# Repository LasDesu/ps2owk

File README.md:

# ps2owk
PS/2 to One-Wire-Keyboard adapter.

Adapter for various retro computer keyboards using only one wire for data transfer. One hardware - multiple firmware.
Currently supported:
- PC-8801MA (type C keyboard, I guess)
- FM-77AV

Original project page: http://zxdesu.byethost32.com/2018/02/13/pc-8801-keyboard-adapter/

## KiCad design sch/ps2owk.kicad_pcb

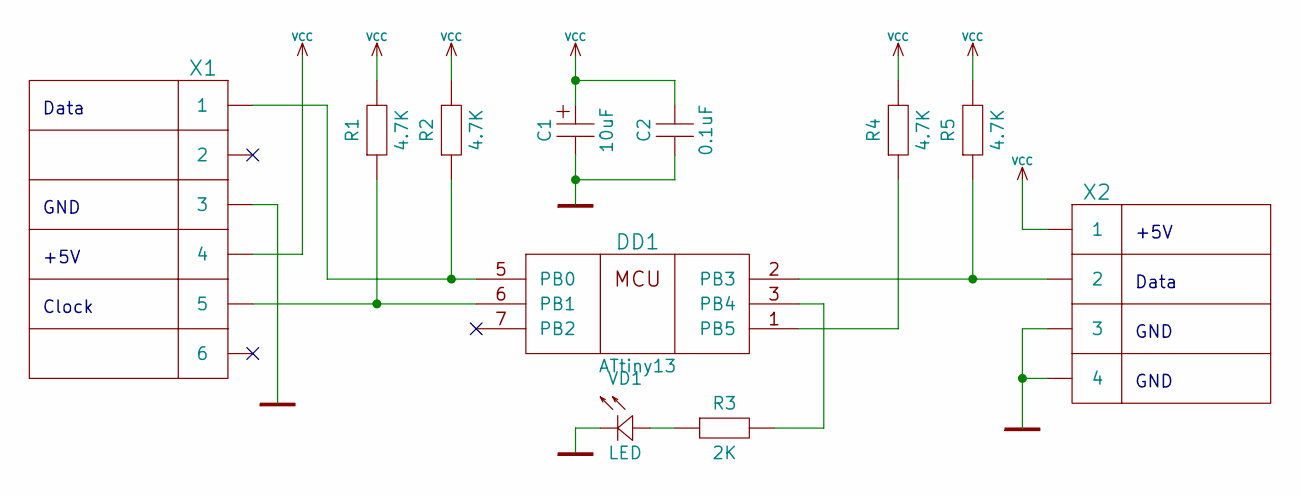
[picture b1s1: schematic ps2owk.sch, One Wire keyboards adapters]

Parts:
C1: 10uF; CP_Radial_D5.0mm_P2.50mm
C2: 0.1uF; C_0805_HandSoldering
DD1: ATtiny13; DIP-8
R1, R2, R4, R5: 4.7K; R_0805_HandSoldering
R3: 2K; R_0805_HandSoldering
VD1: LED; LED_D3.0mm
X1: CONN-6; Mini_din6
X2: CONN-4; Socket_Strip_Straight_1x04_Pitch2.54mm

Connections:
GND: C1.2, C2.1, DD1.4 (GND), VD1.1, X1.3, X2.3, X2.4
unnamed: DD1.1 (PB5), R4.1
unnamed: DD1.2 (PB3), R5.1, X2.2
unnamed: DD1.3 (PB4), R3.2
unnamed: DD1.5 (PB0), R2.1, X1.1
unnamed: DD1.6 (PB1), R1.1, X1.5
unnamed: R3.1, VD1.2
VCC: C1.1, C2.2, DD1.8 (VCC), R1.2, R2.2, R4.2, R5.2, X1.4, X2.1

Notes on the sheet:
Data
GND
+5V
Clock

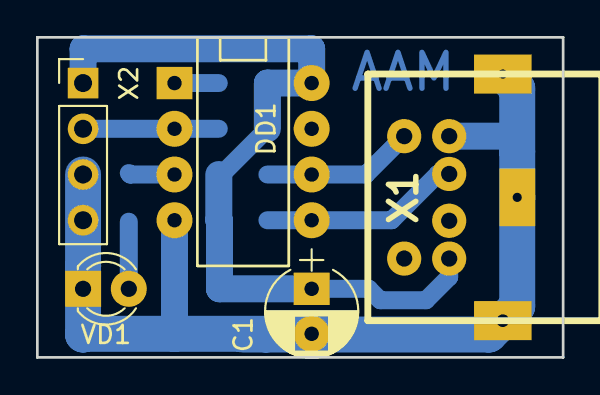
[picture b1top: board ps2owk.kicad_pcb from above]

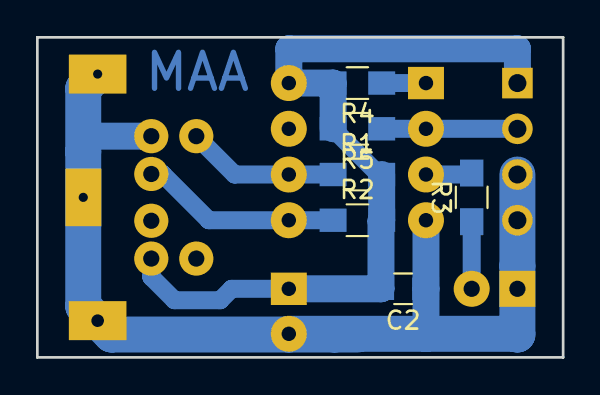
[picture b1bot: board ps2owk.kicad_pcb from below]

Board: 2 copper layers, 29.2 x 17.8 mm, 11 parts (6 on the bottom side), 8 nets.

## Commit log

2018-02-16 testing .editorconfig
2018-02-17 fix sysfreq on tiny13; fix F7 key
2018-02-17 element values
2019-05-06 Update README.md
    Project rename
2019-05-06 Rename KiCad files
2019-05-06 hw: update schematic
2019-05-06 PC88: move firmware to subfolder
2019-05-06 PC88: make LED flashing more distinct
2019-05-06 FM77: initial commit
2019-05-06 Fix type in readme
2019-05-07 Fix typo in readme
2019-05-07 FM77: use open emitter instead of push-pull
2019-05-07 FM77: place ESC and Break keys more like in original keyboard
2019-05-07 X1: initial commit, not finished
